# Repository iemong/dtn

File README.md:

# Desktop Noroshi (DTN)
DTNとはオープンソースのIoT狼煙デバイスです。親機と子機で構成されています。
親機はintel Edisonとtwe-liteで構成されています。(確認はしてませんが、Node.jsが動けば動作すると思うのでRaspberry Piでも動作すると思います)
子機はArduino Pro Miniとtwe-liteとSolid State Relayで構成されています。(その内、チップを全部SMDにして基盤をまとめます)。mraaライブラリを使っているので、intel Edisonの代わりにRaspberry piなども使えます。

## dependency
+ node v4.4.3
+ npm   4.0.2
+ Arduino  1.6.9~

## device
Use a lasor cutter and CNC miling machine to make this device.

### material
+ 3mm acrylic
+ 4mm MDF

### parts list
+ [Arduino Pro Mini 3.3V 8Mhz](https://www.sparkfun.com/products/11114)
+ [TWE-Lite DIP](http://akizukidenshi.com/catalog/g/gM-06760/)
+ [SSR kit](http://akizukidenshi.com/catalog/g/gK-00203/)
+ [MINI USB cable](https://www.amazon.co.jp/gp/product/B00068KUX8/ref=oh_aui_detailpage_o08_s00?ie=UTF8&psc=1)
+ [15mm small FAN](http://store.shopping.yahoo.co.jp/vshopu/2168-1301.html?sc_e=slga_pla)
+ [パナソニック トリプルタップ1500 B/P WH2013BP](https://www.amazon.co.jp/gp/product/B007CW3010/ref=oh_aui_detailpage_o05_s00?ie=UTF8&psc=1)
+ [サンワサプライ 超小型USB充電器(1A出力・ホワイト) ACA-IP32WN](https://www.amazon.co.jp/gp/product/B01A89GJ70/ref=oh_aui_detailpage_o09_s00?ie=UTF8&psc=1)
+ [Mini USBコネクタ](http://akizukidenshi.com/catalog/g/gC-05843/)
+ [メスピンヘッダ](http://akizukidenshi.com/catalog/g/gC-10073/) x 2
+ 4mm ボルト x 6
+ 霧化ユニット USH-400 (ECO)
+ 抵抗 5kΩ 1/4w
+ [電源トランス](http://toei-trans.jp/?pid=91217150)

## program
`cd program/server/noroc_server/`

`npm install`

`node bin/www`

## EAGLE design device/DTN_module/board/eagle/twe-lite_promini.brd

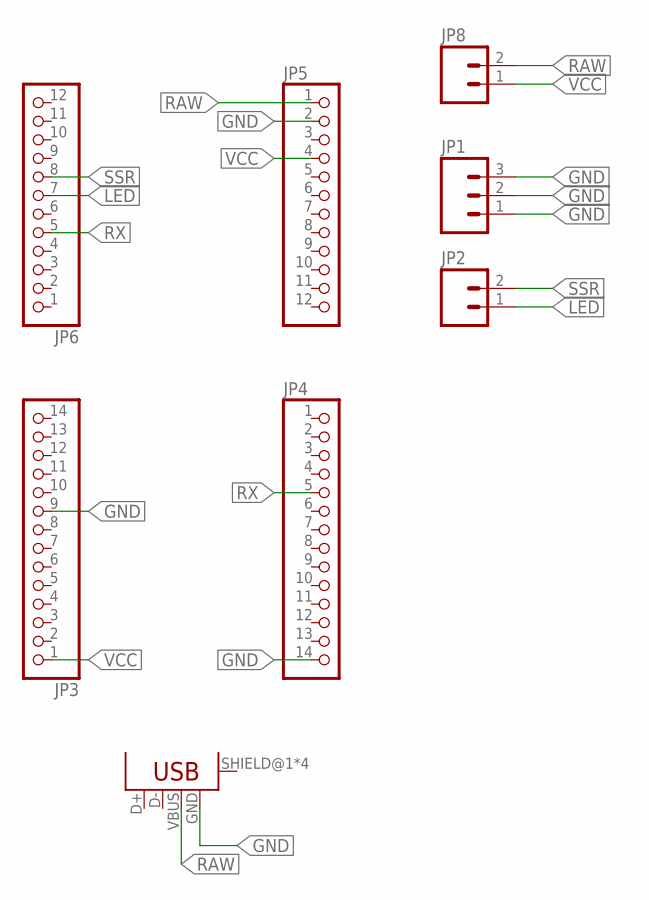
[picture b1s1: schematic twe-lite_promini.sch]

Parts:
JP1: M03PTH; 1X03
JP2, JP8: M02PTH; 1X02
JP3, JP4: PINHD-1X14-CB; 1X14-CB
JP5, JP6: PINHD-1X12-CB; 1X12-CB
U$1: USB_MINIB

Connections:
GND: JP1.1, JP1.2, JP1.3, JP3.9, JP4.14, JP5.2, U$1.GND
LED: JP2.1, JP6.7
RAW: JP5.1, JP8.2, U$1.VBUS
RX: JP4.5, JP6.5
SSR: JP2.2, JP6.8
VCC: JP3.1, JP5.4, JP8.1

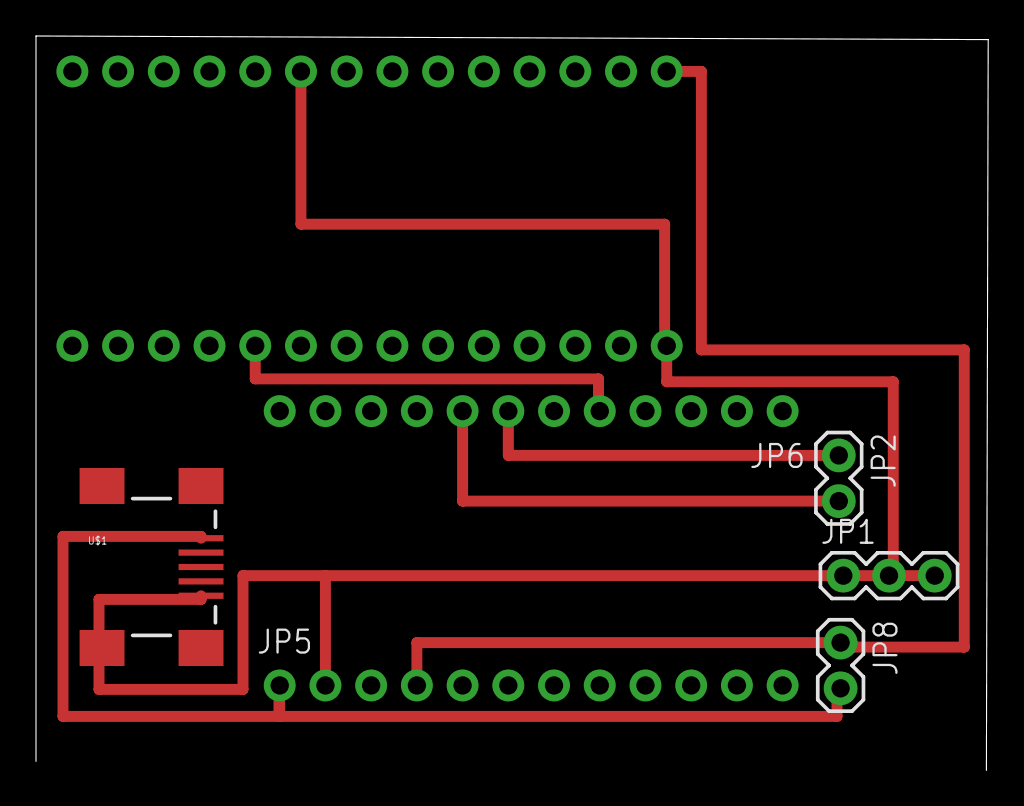
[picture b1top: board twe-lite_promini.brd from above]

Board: 2 copper layers, 52.9 x 40.8 mm, 8 parts (0 on the bottom side), 6 nets.

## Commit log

2017-01-25 いらんやつ消した

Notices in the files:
parts and their libraries:
01_SparkFun: Licensing: CC v3.0 Share-Alike You are welcome to use this library for commercial purposes.
